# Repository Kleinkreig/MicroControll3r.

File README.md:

MicroControll3r
================

What is this?
-------------

**MicroControll3r.** is a keyboard designed to be simple. It's a keyboard powered by the **Raspberry Pi RP2040**.

You can use it as a macro pad for your PC.

The Specs
---------

-   **CPU:** Raspberry Pi RP2040 (Dual-core ARM Cortex M0+)

-   **Ports:** USB-C (Power & Data)

-   **Power:** USB 5V

Required Parts
----------------------------------------------
-  Seeed XIAO RP2040 (x1)
-  SK6812 MINI-E LEDs (x4)
-  Blank DSA keycaps/Any Mechanical Keyboard Keycap (x4)
-  MX-Style switches (x4)
-  Soldering Iron (x1)

NOTE: I did not want to create a case as I prefer it case-less. This is also my first experience with CAD and designing PCBs so judge this project as just a test.

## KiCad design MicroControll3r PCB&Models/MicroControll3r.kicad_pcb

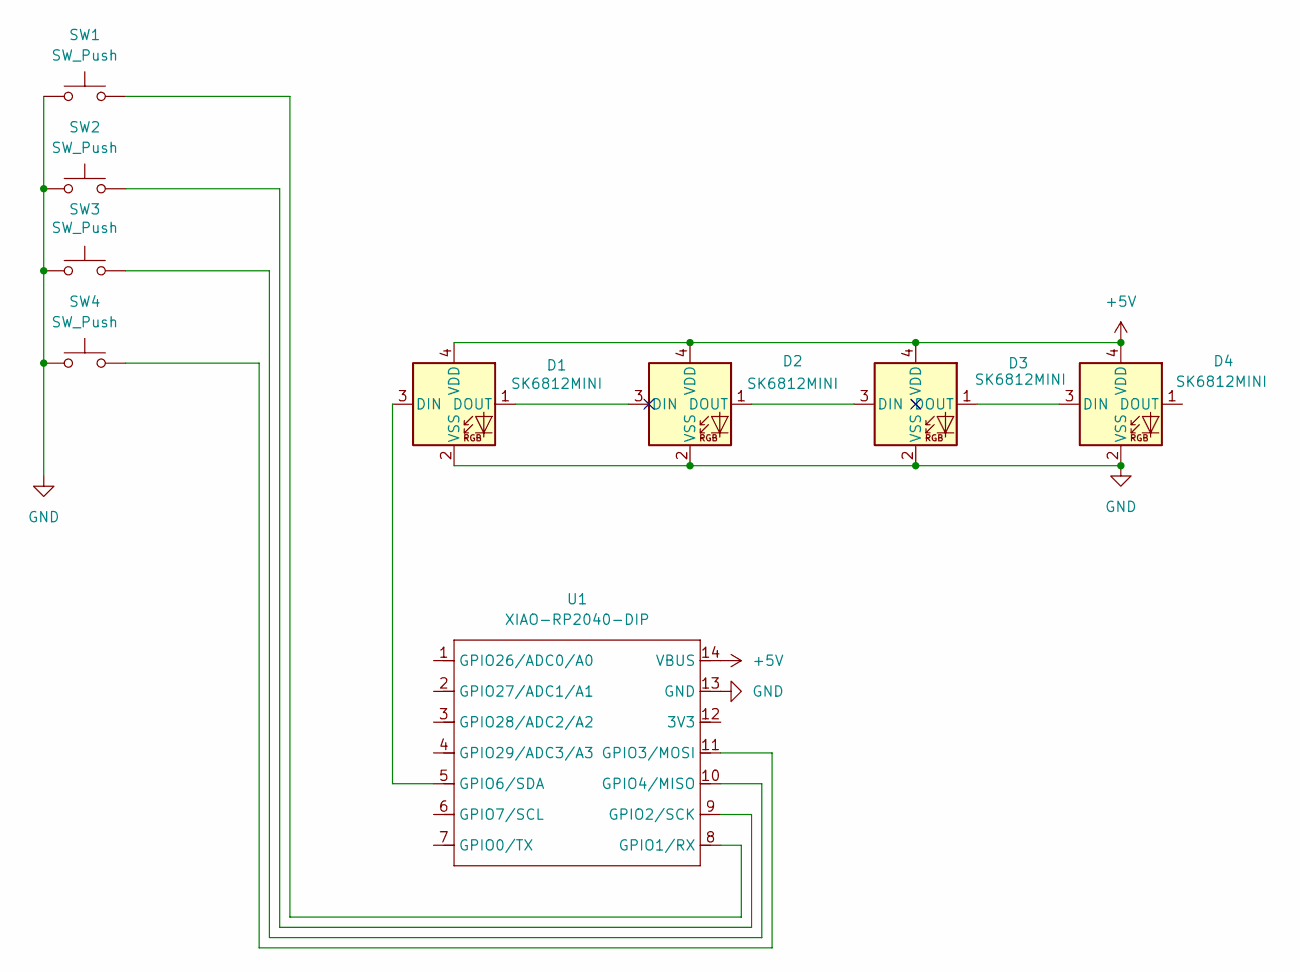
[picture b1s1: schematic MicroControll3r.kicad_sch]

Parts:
D1, D2, D3, D4: SK6812MINI; LED_SK6812MINI_PLCC4_3.5x3.5mm_P1.75mm
SW1, SW2, SW3, SW4: SW_Push; SW_Cherry_MX_1.00u_PCB
U1: XIAO-RP2040-DIP

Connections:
+5V: D1.4 (VDD), D2.4 (VDD), D3.4 (VDD), D4.4 (VDD), U1.14 (VBUS)
GND: D1.2 (VSS), D2.2 (VSS), D3.2 (VSS), D4.2 (VSS), SW1.1, SW2.1, SW3.1, SW4.1, U1.13 (GND)
unnamed: D1.3 (DIN), U1.5 (GPIO6/SDA)
unnamed: D1.1 (DOUT), D2.3 (DIN)
unnamed: D2.1 (DOUT), D3.3 (DIN)
unnamed: D3.1 (DOUT), D4.3 (DIN)
unnamed: SW1.2, U1.8 (GPIO1/RX)
unnamed: SW2.2, U1.9 (GPIO2/SCK)
unnamed: SW4.2, U1.11 (GPIO3/MOSI)
unnamed: SW3.2, U1.10 (GPIO4/MISO)

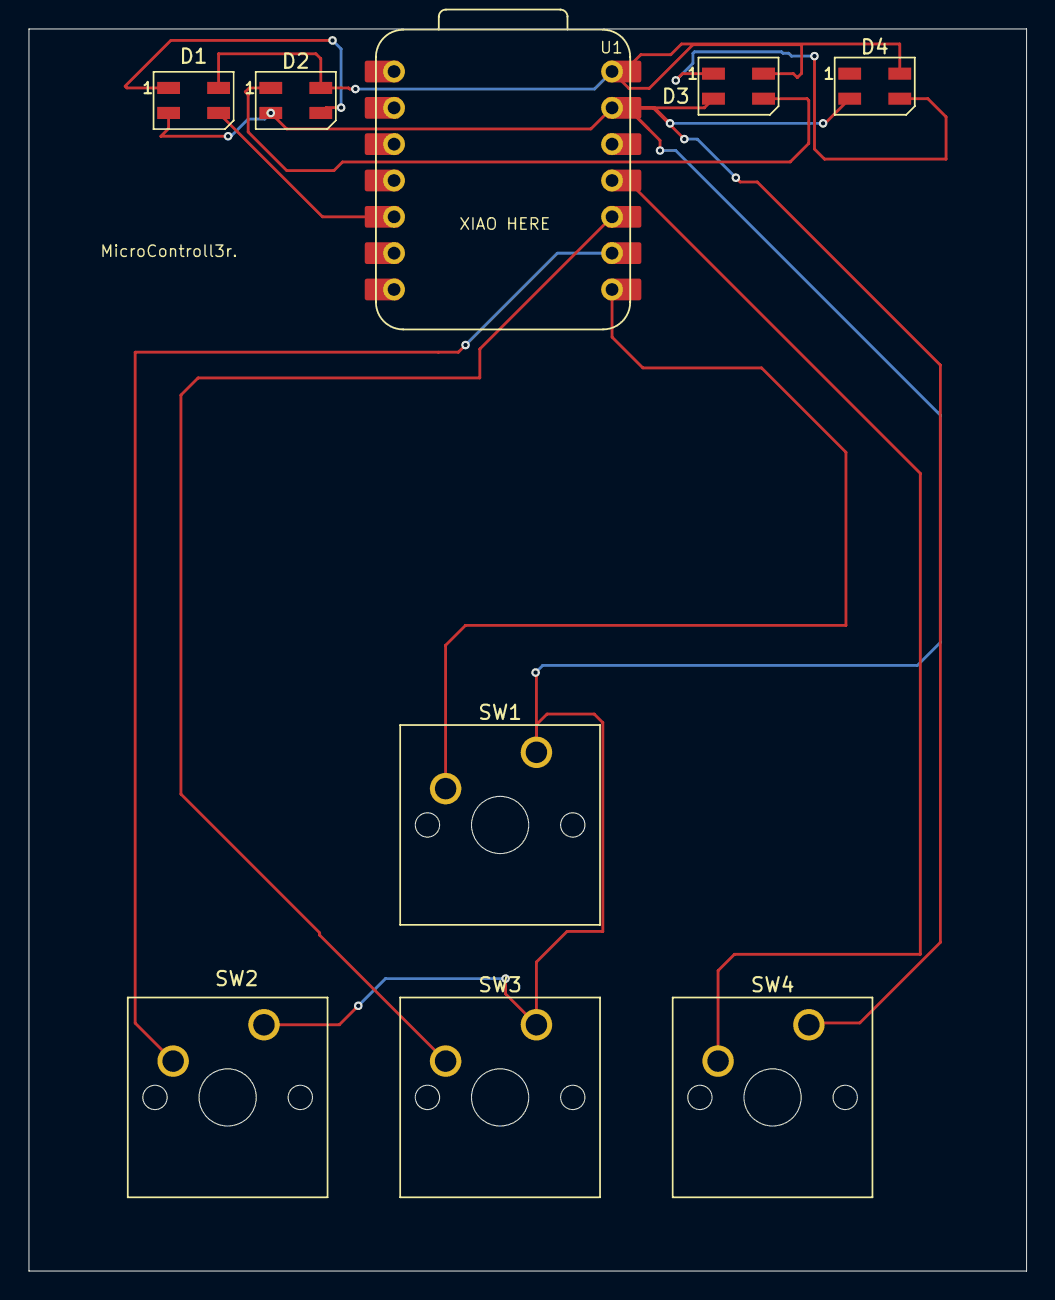
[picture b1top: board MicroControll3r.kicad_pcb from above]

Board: 2 copper layers, 69.8 x 86.8 mm, 9 parts (0 on the bottom side), 10 nets.

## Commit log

2025-12-05 Enhance README with project details and features
    Expanded the README to provide detailed information about the MicroControll3r, including its features and specifications.
2025-12-05 Remove image from README
2025-12-05 Add project status note to README
    Added a note about the project's status and future plans.
2025-12-06 Fix formatting in README header
2025-12-06 Added 3D Models
2025-12-06 Update wording in README for clarity
2025-12-06 Added More Files including firmware
2025-12-06 Update README with required parts list
    Added a list of required parts for the project.
2025-12-06 Add Firmware.mpy file
2025-12-07 Add more screenshots to README
    Added additional screenshots to the README.
2025-12-07 Remove image from README.md
    Removed an image tag from the README file.
2025-12-08 Updated PCB models
2025-12-08 Update keycap description in README
